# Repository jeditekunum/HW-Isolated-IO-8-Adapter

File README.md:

## Isolated 8 Channel I/O Adapter for Elexol et al

This project is documented at [Isolated 8 I/O Adapter for Elexol et al](http://www.jeditekunum.com/Articles/2018/Isolated-8-IO-Adapter-Elexol/).

## Boards

<a href="https://oshpark.com/shared_projects/lH7jXZF9"></img></a>

## License

<br />This work is licensed under a <a rel="license" href="http://creativecommons.org/licenses/by-nc-sa/3.0/">Creative Commons Attribution-NonCommercial-ShareAlike 3.0 Unported License</a>.

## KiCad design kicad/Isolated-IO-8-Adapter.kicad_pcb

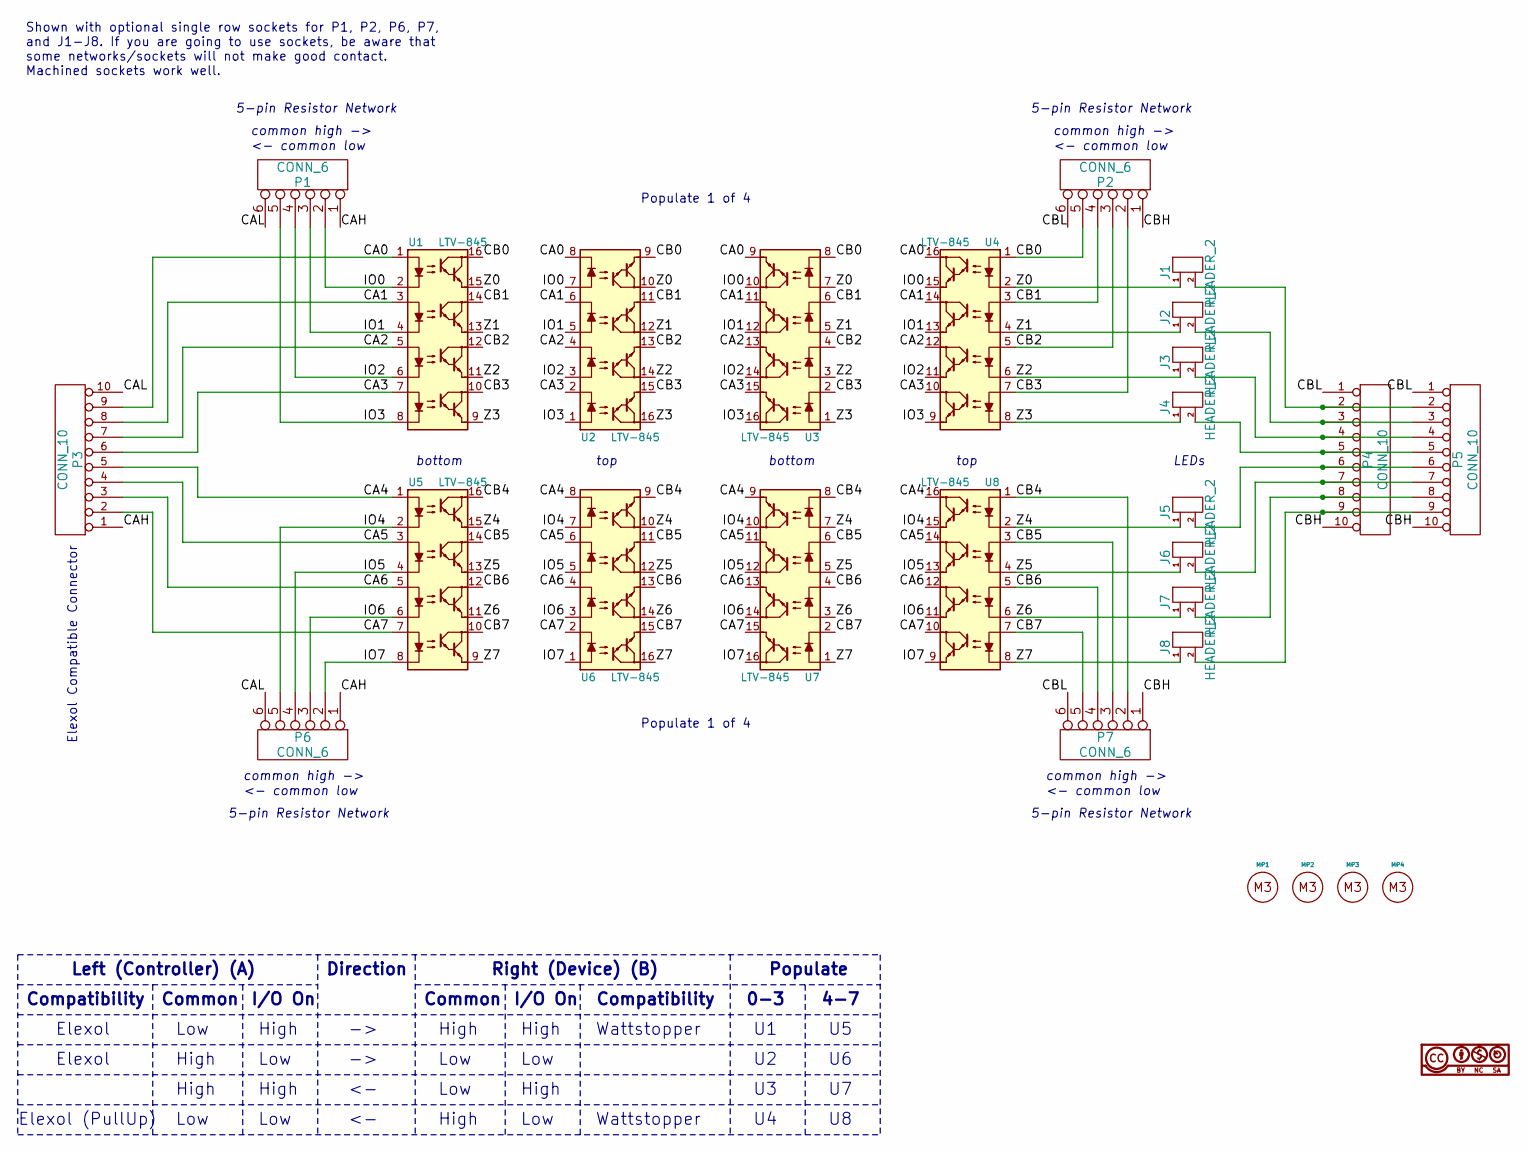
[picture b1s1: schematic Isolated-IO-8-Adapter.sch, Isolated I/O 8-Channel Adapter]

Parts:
J1, J2, J3, J4, J5, J6, J7, J8: HEADER_2; Socket_Strip_Straight_1x02_Pitch2.54mm
LIC1: CC-BY-NC-SA-icon; Logo_silk_CC-BY-NC-SA_10x3.6mm
MP1, MP2, MP3, MP4: MECH_NPTH_M3; MountingHole_3.2mm_M3
P1, P2, P6, P7: CONN_6; Socket_Strip_Straight_1x06_Pitch2.54mm
P3: CONN_10; vasch_strip_5x2
P4: CONN_10; KF141V-10P
P5: CONN_10; pt_1,5-10-3,5-h
U1, U2, U3, U4, U5, U6, U7, U8: LTV-845; DIP-16_W7.62mm

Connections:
/CA0: P3.9, U1.1, U2.8, U3.9, U4.16
/CA1: P3.8, U1.3, U2.6, U3.11, U4.14
/CA2: P3.7, U1.5, U2.4, U3.13, U4.12
/CA3: P3.6, U1.7, U2.2, U3.15, U4.10
/CA4: P3.5, U5.1, U6.8, U7.9, U8.16
/CA5: P3.4, U5.3, U6.6, U7.11, U8.14
/CA6: P3.3, U5.5, U6.4, U7.13, U8.12
/CA7: P3.2, U5.7, U6.2, U7.15, U8.10
/CAH: P1.1, P3.1, P6.1
/CAL: P1.6, P3.10, P6.6
/CB0: P2.5, U1.16, U2.9, U3.8, U4.1
/CB1: P2.4, U1.14, U2.11, U3.6, U4.3
/CB2: P2.3, U1.12, U2.13, U3.4, U4.5
/CB3: P2.2, U1.10, U2.15, U3.2, U4.7
/CB4: P7.2, U5.16, U6.9, U7.8, U8.1
/CB5: P7.3, U5.14, U6.11, U7.6, U8.3
/CB6: P7.4, U5.12, U6.13, U7.4, U8.5
/CB7: P7.5, U5.10, U6.15, U7.2, U8.7
/CBH: P2.1, P4.10, P5.10, P7.1
/CBL: P2.6, P4.1, P5.1, P7.6
/IO0: P1.2, U1.2, U2.7, U3.10, U4.15
/IO1: P1.3, U1.4, U2.5, U3.12, U4.13
/IO2: P1.4, U1.6, U2.3, U3.14, U4.11
/IO3: P1.5, U1.8, U2.1, U3.16, U4.9
/IO4: P6.5, U5.2, U6.7, U7.10, U8.15
/IO5: P6.4, U5.4, U6.5, U7.12, U8.13
/IO6: P6.3, U5.6, U6.3, U7.14, U8.11
/IO7: P6.2, U5.8, U6.1, U7.16, U8.9
/Z0: J1.1, U1.15, U2.10, U3.7, U4.2
/Z1: J2.1, U1.13, U2.12, U3.5, U4.4
/Z2: J3.1, U1.11, U2.14, U3.3, U4.6
/Z3: J4.1, U1.9, U2.16, U3.1, U4.8
/Z4: J5.1, U5.15, U6.10, U7.7, U8.2
/Z5: J6.1, U5.13, U6.12, U7.5, U8.4
/Z6: J7.1, U5.11, U6.14, U7.3, U8.6
/Z7: J8.1, U5.9, U6.16, U7.1, U8.8
unnamed: J1.2, P4.2, P5.2
unnamed: J2.2, P4.3, P5.3
unnamed: J3.2, P4.4, P5.4
unnamed: J4.2, P4.5, P5.5
unnamed: J5.2, P4.6, P5.6
unnamed: J6.2, P4.7, P5.7
unnamed: J7.2, P4.8, P5.8
unnamed: J8.2, P4.9, P5.9

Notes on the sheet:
Left (Controller) (A)
Right (Device) (B)
Direction
Common
High
Low
I/O On
0-3
4-7
Populate
5-pin Resistor Network
common high ->
<- common low
Elexol (PullUp)
Elexol
Wattstopper
Compatibility
Elexol Compatible Connector
top
bottom
LEDs
Populate 1 of 4
Shown with optional single row sockets for P1, P2, P6, P7, and J1-J8. If you are going to use sockets, be aware that some networks/sockets will not make good contact. Machined sockets work well.

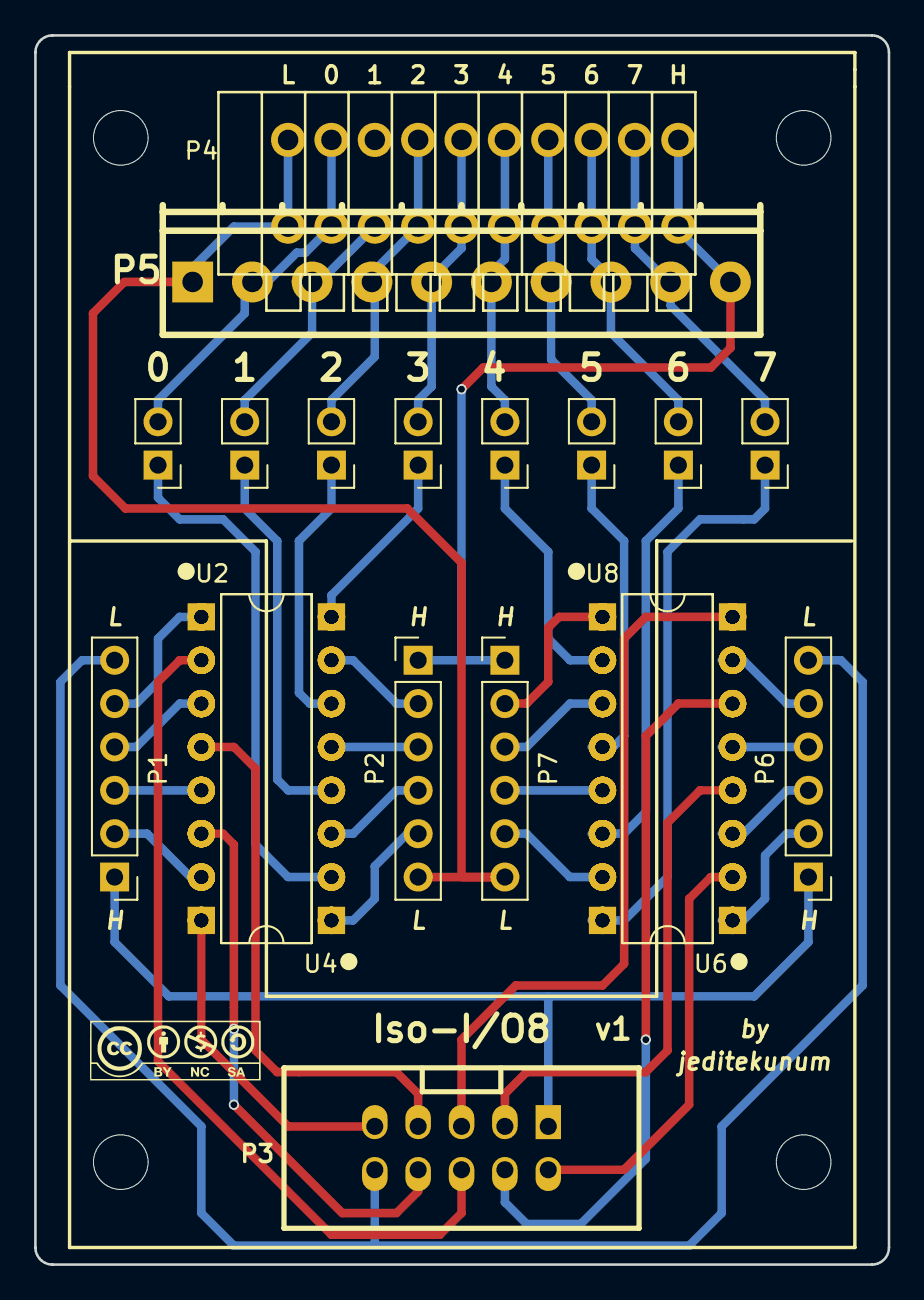
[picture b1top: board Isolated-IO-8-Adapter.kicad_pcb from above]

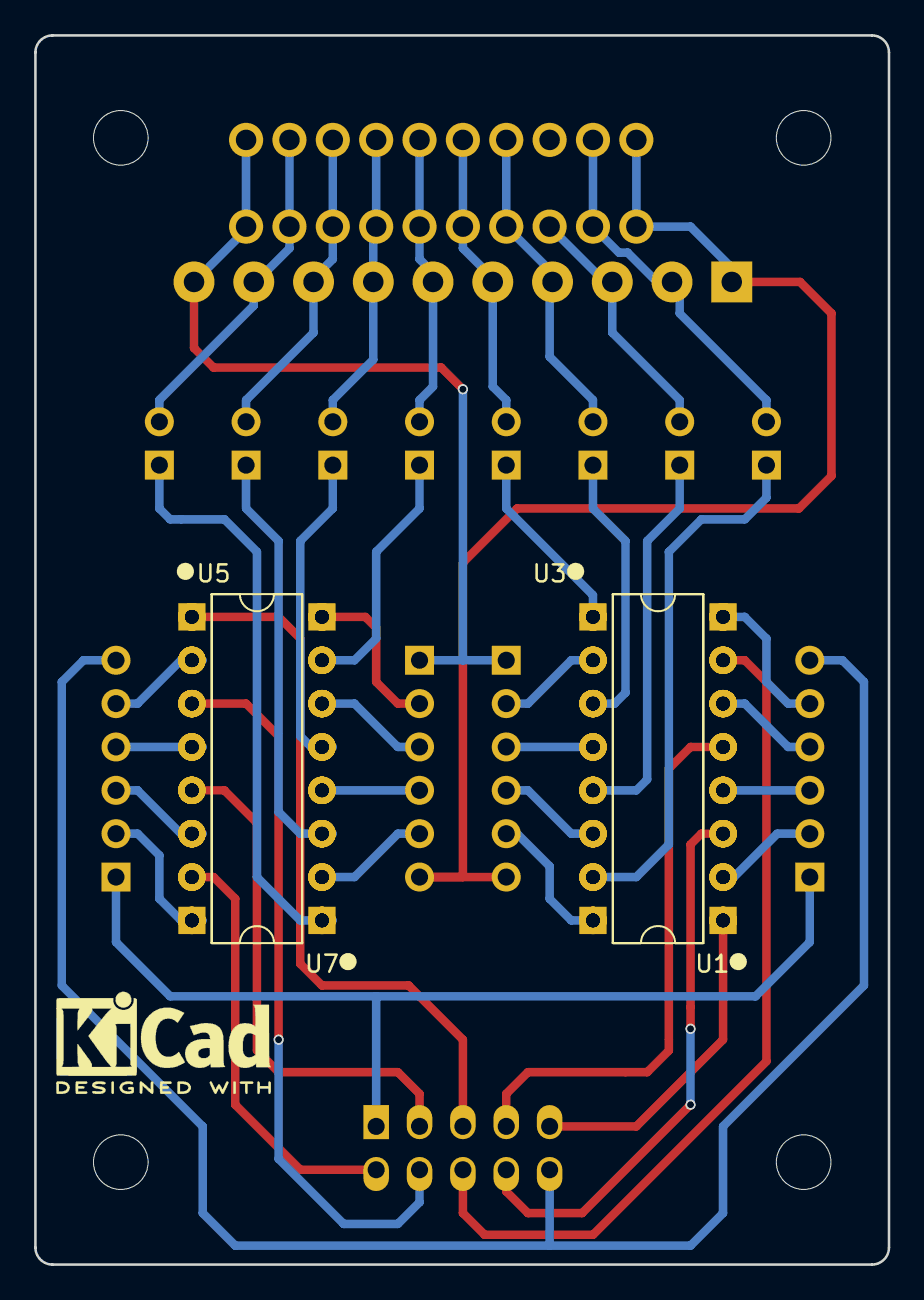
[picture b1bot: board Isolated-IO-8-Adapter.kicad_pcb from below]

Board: 2 copper layers, 50.0 x 72.0 mm, 28 parts (4 on the bottom side), 44 nets.

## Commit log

2018-01-10 Initial publication
